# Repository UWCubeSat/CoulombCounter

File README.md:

# coulomb-counter
Evaluation board to send the bus voltage and accumulated charge from a battery to the MSP430. 
It does this by monitoring voltage developed across a sense resistor. Differential voltage between
the SENSE+ and SENSE- pins is applied to an auto-zeroed differential analog integrater to track charge.
For precision, the sensor should maintain below a threshold of 50mV

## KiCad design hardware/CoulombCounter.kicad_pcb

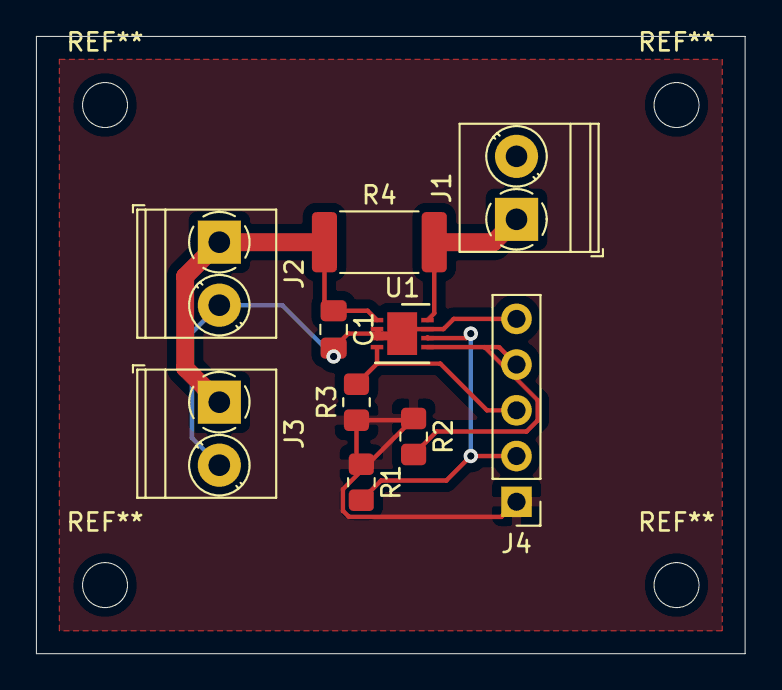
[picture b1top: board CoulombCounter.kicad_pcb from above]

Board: 2 copper layers, 39.4 x 34.3 mm, 10 parts (0 on the bottom side), 7 nets.

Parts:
C1: 1u; C_0805_2012Metric_Pad1.18x1.45mm_HandSolder
J1, J2, J3: Screw_Terminal_01x02; TerminalBlock_Phoenix_PT-1,5-2-3.5-H_1x02_P3.50mm_Horizontal
J4: Conn_01x05_Male; PinHeader_1x05_P2.54mm_Vertical
R1, R2, R3: 2k; R_0805_2012Metric_Pad1.20x1.40mm_HandSolder
R4: 50m; R_2512_6332Metric_Pad1.40x3.35mm_HandSolder
U1: LTC2943; DFN-8-1EP_3x3mm_P0.5mm_EP1.66x2.38mm

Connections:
+3V3: J4.1, R1.1, R2.1, R3.1
+VDC: J1.1, R4.2, U1.8
/SCL: J4.3, R3.2, U1.4
/SDA: J4.4, R2.2, U1.5
/~ALCC~: J4.2, R1.2, U1.6
GND: C1.2, J1.2, J2.2, J3.2, J4.5, U1.2, U1.3, U1.7, U1.9
unnamed: C1.1, J2.1, J3.1, R4.1, U1.1

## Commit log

2020-12-14 Created PCB
2020-12-18 Fixed shorting PWR and GND, references and values, and silkscreen
2020-12-18 Added silkscreen
2021-02-01 Rename CoulombCounter-cache.lib to hardware/CoulombCounter-cache.lib
2021-02-01 Rename CoulombCounter.kicad_pcb to hardware/CoulombCounter.kicad_pcb
2021-02-01 Rename CoulombCounter.net to hardware/CoulombCounter.net
2021-02-01 Rename CoulombCounter.pro to hardware/CoulombCounter.pro
2021-02-01 Rename CoulombCounter.sch to hardware/CoulombCounter.sch
2021-02-01 Rename CoulombCounter.sch-bak to hardware/CoulombCounter.sch-bak
2021-02-01 Rename CoulombCounter2.net to hardware/CoulombCounter2.net
2021-02-01 Rename LTC2943.dcm to hardware/LTC2943.dcm
2021-02-01 Rename report.txt to hardware/report.txt
2021-02-01 Rename CoulombCounter.cpp to I2C/CoulombCounter.cpp
2021-02-01 Rename CoulombCounter.h to I2C/CoulombCounter.h
2021-02-01 Rename CoulombCounterTest.ino to I2C/CoulombCounterTest.ino
2021-02-02 Added sources, defines for ESP32 communication
2021-02-07 Added average V, C, and WIRE init
